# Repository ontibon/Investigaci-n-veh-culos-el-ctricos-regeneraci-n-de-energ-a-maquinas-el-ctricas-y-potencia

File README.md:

# Sistemas electrónicos necesarios para la conversión de un vehículo de combustión interna a eléctrico, mediante el control de un motor trifásico, optimizando el uso de la energía mediante el freno regenerativo.

## ¿Qué encontraras en este repositorio? 🚗⚡

_En este repositorio esta almacenado todo lo relacionado al estudio de vehículos eléctricos en Colombia y el planteamiento de los sistemas electrónicos para la conversión de un vehículo convencional a eléctricos, realizando pruebas físicas de regeneración de energía, simulaciones de las maquinas eléctricas que se pueden usar en este tipo de sistemas, simulaciones de las configuraciones de electrónica de potencia para el manejo eficiente de la energía. Entre otros documentos interesantes. 
Esto en el marco del proyecto de investigación realizado por Julian Ontibon. Desde el laboratorio de fuentes alternas de energia [(Lifae)](https://comunidad.udistrital.edu.co/lifae/) de la Universidad Distrital Francisco Jose de Caldas_

## Construido con 🛠️

_Hardware:_

* [Opal RT](https://www.opal-rt.com) - Sistema de control en tiempo real.
* [Leybold](https://www.ld-didactic.de/phk/gruppen.asp?PT=VE2.2.4.2&L=2) - Sistema de pruebas para máquinas eléctricas.
* [Chroma](https://www.chromausa.com/product/bidirectional-dc-power-supply-62000d/) - Fuente DC bidireccional, con carga regenerativa.
* [Semikron](https://www.semikron-danfoss.com/products/product-classes/igbt-driver.html) - Convertidores de potencia con IGBT.

_Software:_

* [Matlab Simulink](https://la.mathworks.com/products/simulink.html)
* [RT Lab](https://www.opal-rt.com/software-rt-lab/)
* [Chroma 62000D SoftPanel](https://www.chromaate.com/en/product/graphical_user_interface_62000d_softpanel_356)
* [Autodesk Eagle](https://www.autodesk.com/products/eagle/overview?term=1-YEAR&tab=subscription)

## Documento Final 📖

Puedes encontrar el documento final de esta investigación junto con el codgio fuente en latex en el siguiete [Overleaf](https://es.overleaf.com/read/zrgrrzybnbwg)

## Autores ✒️

* **Julian David [Ontibon](https://github.com/ontibon) Velasquez** 

## Licencia 📄

Este proyecto está bajo la Licencia Atribución-NoComercial-CompartirIgual 4.0 Internacional - mira el archivo [LICENSE.md](LICENSE.md) para detalles

<br /><span xmlns:dct="http://purl.org/dc/terms/" href="http://purl.org/dc/dcmitype/Dataset" property="dct:title" rel="dct:type">Investigación vehículos eléctricos, regeneración de energía, maquinas eléctricas y  electrónica de potencia</span> por <a xmlns:cc="http://creativecommons.org/ns#" href="https://github.com/ontibon/Investigacion-vehiculos-electricos-regeneracion-de-energia-maquinas-electricas-y-potencia" property="cc:attributionName" rel="cc:attributionURL">Julian David Ontibon Velasquez</a> se distribuye bajo una <a rel="license" href="http://creativecommons.org/licenses/by-nc-sa/4.0/">Licencia Creative Commons Atribución-NoComercial-CompartirIgual 4.0 Internacional</a>.<br />Basada en una obra en <a xmlns:dct="http://purl.org/dc/terms/" href="https://github.com/ontibon/Investigacion-vehiculos-electricos-regeneracion-de-energia-maquinas-electricas-y-potencia" rel="dct:source">https://github.com/ontibon/Investigacion-vehiculos-electricos-regeneracion-de-energia-maquinas-electricas-y-potencia</a>.<br />Permisos más allá del alcance de esta licencia pueden estar disponibles en <a xmlns:cc="http://creativecommons.org/ns#" href="https://www.linkedin.com/in/julian-david-ontibon-velasquez-911242272/" rel="cc:morePermissions">https://www.linkedin.com/in/julian-david-ontibon-velasquez-911242272/</a>.

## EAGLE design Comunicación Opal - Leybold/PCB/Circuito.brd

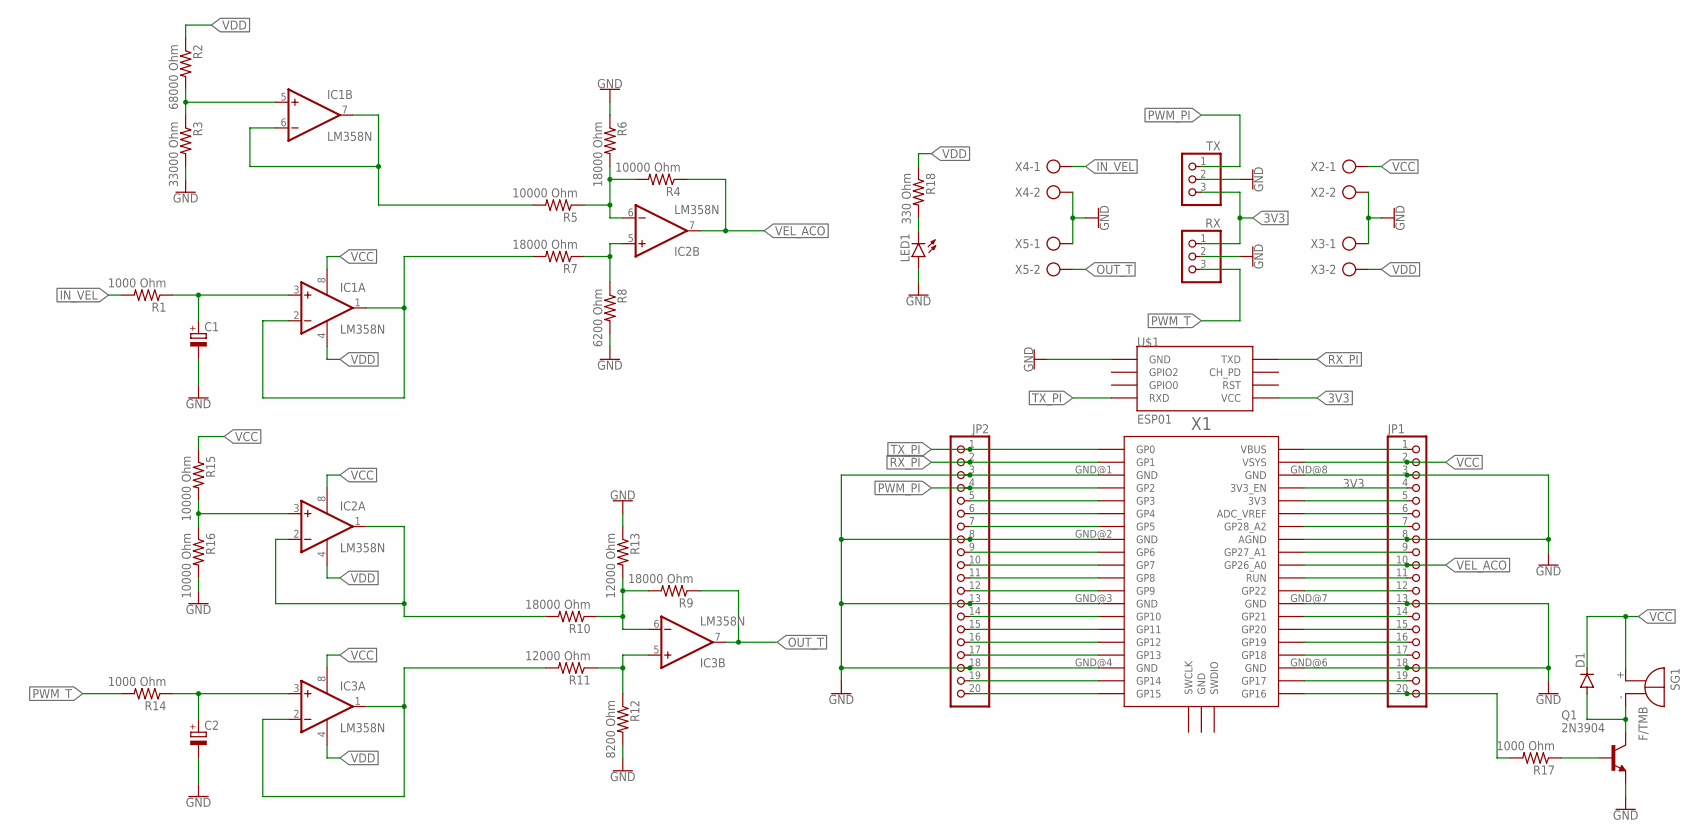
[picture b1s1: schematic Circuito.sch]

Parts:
C1, C2: CPOL-EUE2.5-6; E2,5-6
D1: DIODE-DO15-12; DO15-12
IC1, IC2, IC3: LM358N; DIL08
JP1, JP2: PINHD-1X20; 1X20
LED1: LED3MM
Q1: 2N3904; TO92
R1, R14, R17: 1000 Ohm; 0207/10
R2: 68000 Ohm; 0207/10
R3: 33000 Ohm; 0207/10
R4, R5, R15, R16: 10000 Ohm; 0207/10
R6, R7, R9, R10: 18000 Ohm; 0207/10
R8: 6200 Ohm; 0207/10
R11, R13: 12000 Ohm; 0207/10
R12: 8200 Ohm; 0207/10
R18: 330 Ohm; 0207/10
RX: PINHD-1X3; 1X03
SG1: F/TMB
TX: PINHD-1X3; 1X03
U$1: ESP01
X1: RPI_PICO_IG-TH; RPI_PICO_TH
X2, X3, X4, X5: AK500/2

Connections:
3V3: JP1.4, RX.1, TX.3, U$1.VCC, X1.3V3_EN
GND: C1.-, C2.-, JP1.3, JP1.8, JP1.13, JP1.18, JP2.3, JP2.8, JP2.13, JP2.18, LED1.A, Q1.3 (E), R3.2, R6.1, R8.2, R12.2, R13.1, R16.2, RX.2, TX.2, U$1.GND, X1.AGND, X1.GND@1 (GND), X1.GND@2 (GND), X1.GND@3 (GND), X1.GND@4 (GND), X1.GND@6 (GND), X1.GND@7 (GND), X1.GND@8 (GND), X2.2, X3.1, X4.2, X5.1
IN_VEL: R1.2, X4.1
unnamed: JP1.1, X1.VBUS
unnamed: LED1.K (C), R18.2
unnamed: C1.+, IC1.3 (+IN), R1.1
unnamed: JP1.5, X1.3V3
unnamed: D1.A, Q1.1 (C), SG1.-
unnamed: JP1.6, X1.ADC_VREF
unnamed: JP1.7, X1.GP28_A2
unnamed: IC1.1 (OUT), IC1.2 (-IN), R7.2
unnamed: JP1.9, X1.GP27_A1
unnamed: JP1.11, X1.RUN
unnamed: JP1.12, X1.GP22
unnamed: IC1.6 (-IN), IC1.7 (OUT), R5.2
unnamed: JP1.14, X1.GP21
unnamed: JP1.15, X1.GP20
unnamed: JP1.16, X1.GP19
unnamed: JP1.17, X1.GP18
unnamed: JP1.19, X1.GP17
unnamed: JP1.20, R17.2, X1.GP16
unnamed: IC1.5 (+IN), R2.2, R3.1
unnamed: IC2.6 (-IN), R4.2, R5.1, R6.2
unnamed: IC3.1 (OUT), IC3.2 (-IN), R11.2
unnamed: IC2.5 (+IN), R7.1, R8.1
unnamed: JP2.5, X1.GP3
unnamed: JP2.6, X1.GP4
unnamed: JP2.7, X1.GP5
unnamed: IC3.6 (-IN), R9.2, R10.1, R13.2
unnamed: JP2.9, X1.GP6
unnamed: JP2.10, X1.GP7
unnamed: JP2.11, X1.GP8
unnamed: JP2.12, X1.GP9
unnamed: C2.+, IC3.3 (+IN), R14.1
unnamed: JP2.14, X1.GP10
unnamed: JP2.15, X1.GP11
unnamed: JP2.16, X1.GP12
unnamed: JP2.17, X1.GP13
unnamed: IC3.5 (+IN), R11.1, R12.1
unnamed: JP2.19, X1.GP14
unnamed: JP2.20, X1.GP15
unnamed: IC2.1 (OUT), IC2.2 (-IN), R10.2
unnamed: IC2.3 (+IN), R15.2, R16.1
unnamed: Q1.2 (B), R17.1
OUT_T: IC3.7 (OUT), R9.1, X5.2
PWM_PI: JP2.4, TX.1, X1.GP2
PWM_T: R14.2, RX.3
RX_PI: JP2.2, U$1.TX (TXD), X1.GP1
TX_PI: JP2.1, U$1.RX (RXD), X1.GP0
VCC: D1.C, IC1.8 (V+), IC2.8 (V+), IC3.8 (V+), JP1.2, R15.1, SG1.+, X1.VSYS, X2.1
VDD: IC1.4 (V-), IC2.4 (V-), IC3.4 (V-), R2.1, R18.1, X3.2
VEL_ACO: IC2.7 (OUT), JP1.10, R4.1, X1.GP26_A0

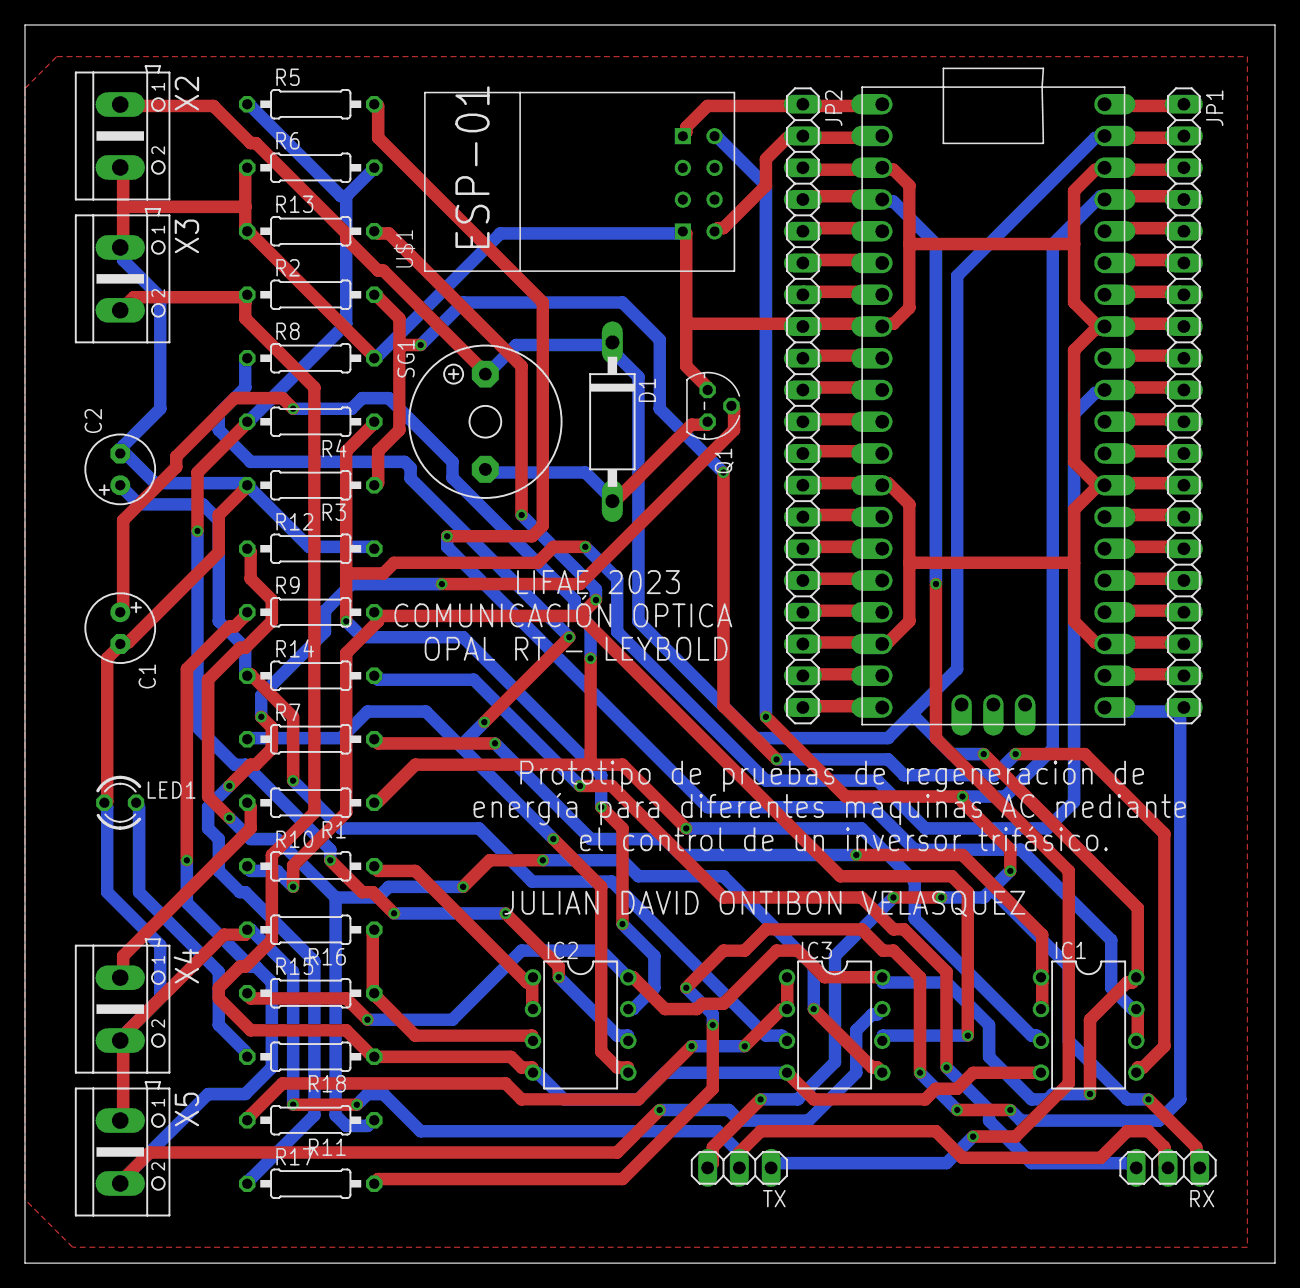
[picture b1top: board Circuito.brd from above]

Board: 2 copper layers, 100.0 x 99.0 mm, 37 parts (0 on the bottom side), 52 nets.

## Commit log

2023-04-16 Rename PCB.md to ¿Qué encontraras en esta carpeta?.md

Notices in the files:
parts and their libraries:
SparkFun-PowerSymbols: Licensing: Creative Commons ShareAlike 4.0 International - https://creativecommons.org/licenses/by-sa/4.0
